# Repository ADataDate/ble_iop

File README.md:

# ble_iop
A Ryan and Mary Bluetooth Low Energy Project

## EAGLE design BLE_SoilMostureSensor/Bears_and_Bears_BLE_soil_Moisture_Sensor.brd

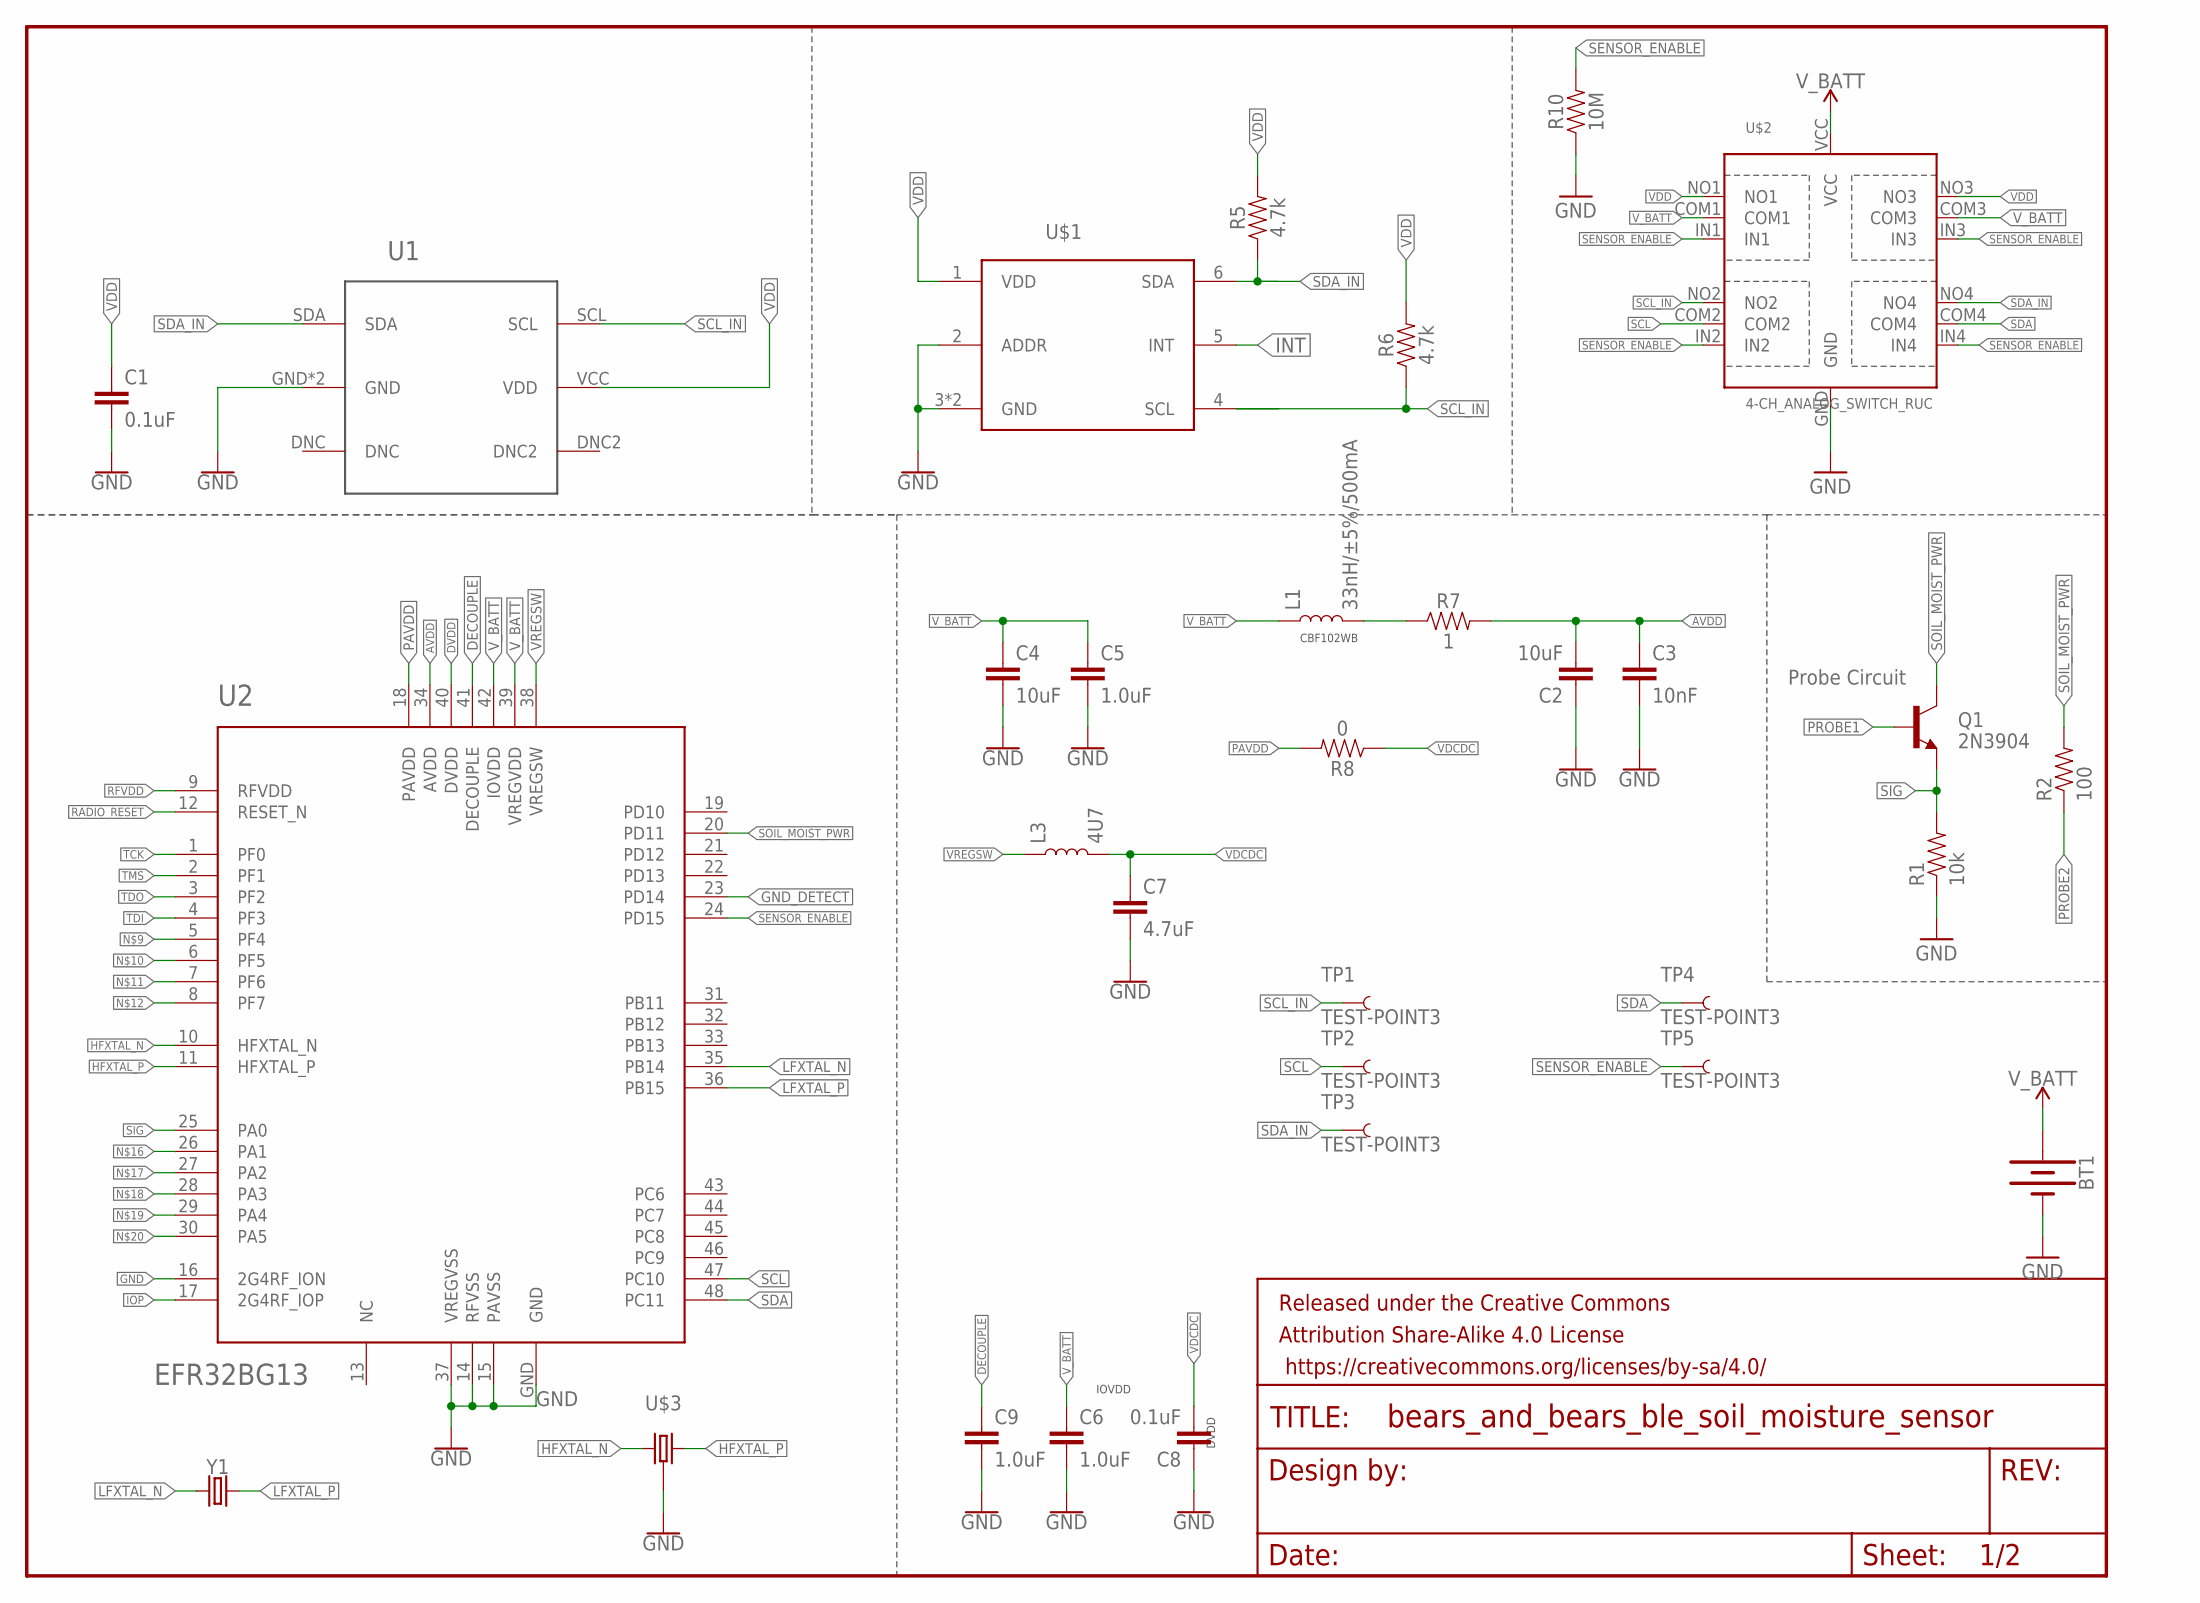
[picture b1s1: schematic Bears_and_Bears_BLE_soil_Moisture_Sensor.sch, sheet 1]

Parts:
BT1: BATTERY-20MM_SMD_4LEGS_OVERPASTE; BATTCON_20MM_4LEGS_OVERPASTE
C1, C8: 0.1uF; 0603
C2, C4: 10uF; 0603
C3: 10nF; 0603
C5, C6, C9: 1.0uF; 0603
C7: 4.7uF; 0603
FRAME1: FRAME-LETTER; CREATIVE_COMMONS
L1: 33nH/±5%/500mA; 0603
L3: 4U7; 1212(3030METRIC)
Q1: 2N3904; SOT23-3
R1: 10k; 0603-RES
R2: 100; 0603-RES
R5, R6: 4.7k; 0603
R7: 1; 0603
R8: 0; 0603
R10: 10M; 0603
TP1, TP2, TP3, TP4, TP5: TEST-POINT3; PAD.03X.03
U1: SI7021_TEMP_HUMIDTY; DFN-6
U2: EFR32BG13; QFN48
U$1: OPT3001DNPT; 6PIN_USON
U$2: 4-CH_ANALOG_SWITCH_RUC; PX2QFN14_RUC
U$3: 38.4MHZ_CRYSTAL; 2.0X1.6
Y1: 32.768KHZ_LOW_FREQ_CRYSTAL; CRYSTAL_1.2X0.6

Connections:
AVDD: C2.2, C3.1, R7.2, U2.34 (AVDD)
DECOUPLE: C9.1, U2.41 (DECOUPLE)
DVDD: U2.40 (DVDD)
GND: BT1.2 (-), C1.2, C2.1, C3.2, C4.2, C5.2, C6.2, C7.2, C8.1, C9.2, R1.1, R10.1, U1.GND, U1.GND2 (GND), U2.14 (RFVSS), U2.15 (PAVSS), U2.16 (2G4RF_ION), U2.37 (VREGVSS), U2.GND, U$1.2 (ADDR), U$1.3 (GND), U$1.GND, U$2.GND, U$3.GND, U$3.GND2 (GND); also elsewhere on the board
GND_DETECT: U2.23 (PD14); also elsewhere on the board
HFXTAL_N: U2.10 (HFXTAL_N), U$3.1
HFXTAL_P: U2.11 (HFXTAL_P), U$3.3 (2)
INT: U$1.5 (INT)
IOP: U2.17 (2G4RF_IOP); also elsewhere on the board
LFXTAL_N: U2.35 (PB14), Y1.P$1 (1)
LFXTAL_P: U2.36 (PB15), Y1.P$2 (2)
unnamed: L1.2, R7.1
PAVDD: R8.2, U2.18 (PAVDD); also elsewhere on the board
PROBE1: Q1.1 (B)
PROBE2: R2.1
RADIO_RESET: U2.12 (RESET_N); also elsewhere on the board
RFVDD: U2.9 (RFVDD); also elsewhere on the board
SCL: TP2.P$1, U2.47 (PC10), U$2.COM2
SCL_IN: R6.1, TP1.P$1, U1.SCL, U$1.4 (SCL), U$2.NO2
SDA: TP4.P$1, U2.48 (PC11), U$2.COM4
SDA_IN: R5.1, TP3.P$1, U1.SDA, U$1.6 (SDA), U$2.NO4
SENSOR_ENABLE: R10.2, TP5.P$1, U2.24 (PD15), U$2.IN1, U$2.IN2, U$2.IN3, U$2.IN4
SIG: Q1.2 (E), R1.2, U2.25 (PA0)
SOIL_MOIST_PWR: Q1.3 (C), R2.2, U2.20 (PD11)
TCK: U2.1 (PF0); also elsewhere on the board
TDI: U2.4 (PF3); also elsewhere on the board
TDO: U2.3 (PF2); also elsewhere on the board
TMS: U2.2 (PF1); also elsewhere on the board
VDCDC: C7.1, C8.2, L3.P$2 (2), R8.1; also elsewhere on the board
VDD: C1.1, R5.2, R6.2, U1.VCC (VDD), U$1.1 (VDD), U$2.NO1, U$2.NO3; also elsewhere on the board
VREGSW: L3.P$1 (1), U2.38 (VREGSW)
V_BATT: BT1.1 (+), C4.1, C5.1, C6.1, L1.1, U2.39 (VREGVDD), U2.42 (IOVDD), U$2.COM1, U$2.COM3, U$2.VCC

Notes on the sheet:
Probe Circuit
CBF102WB
IOVDD
DVDD

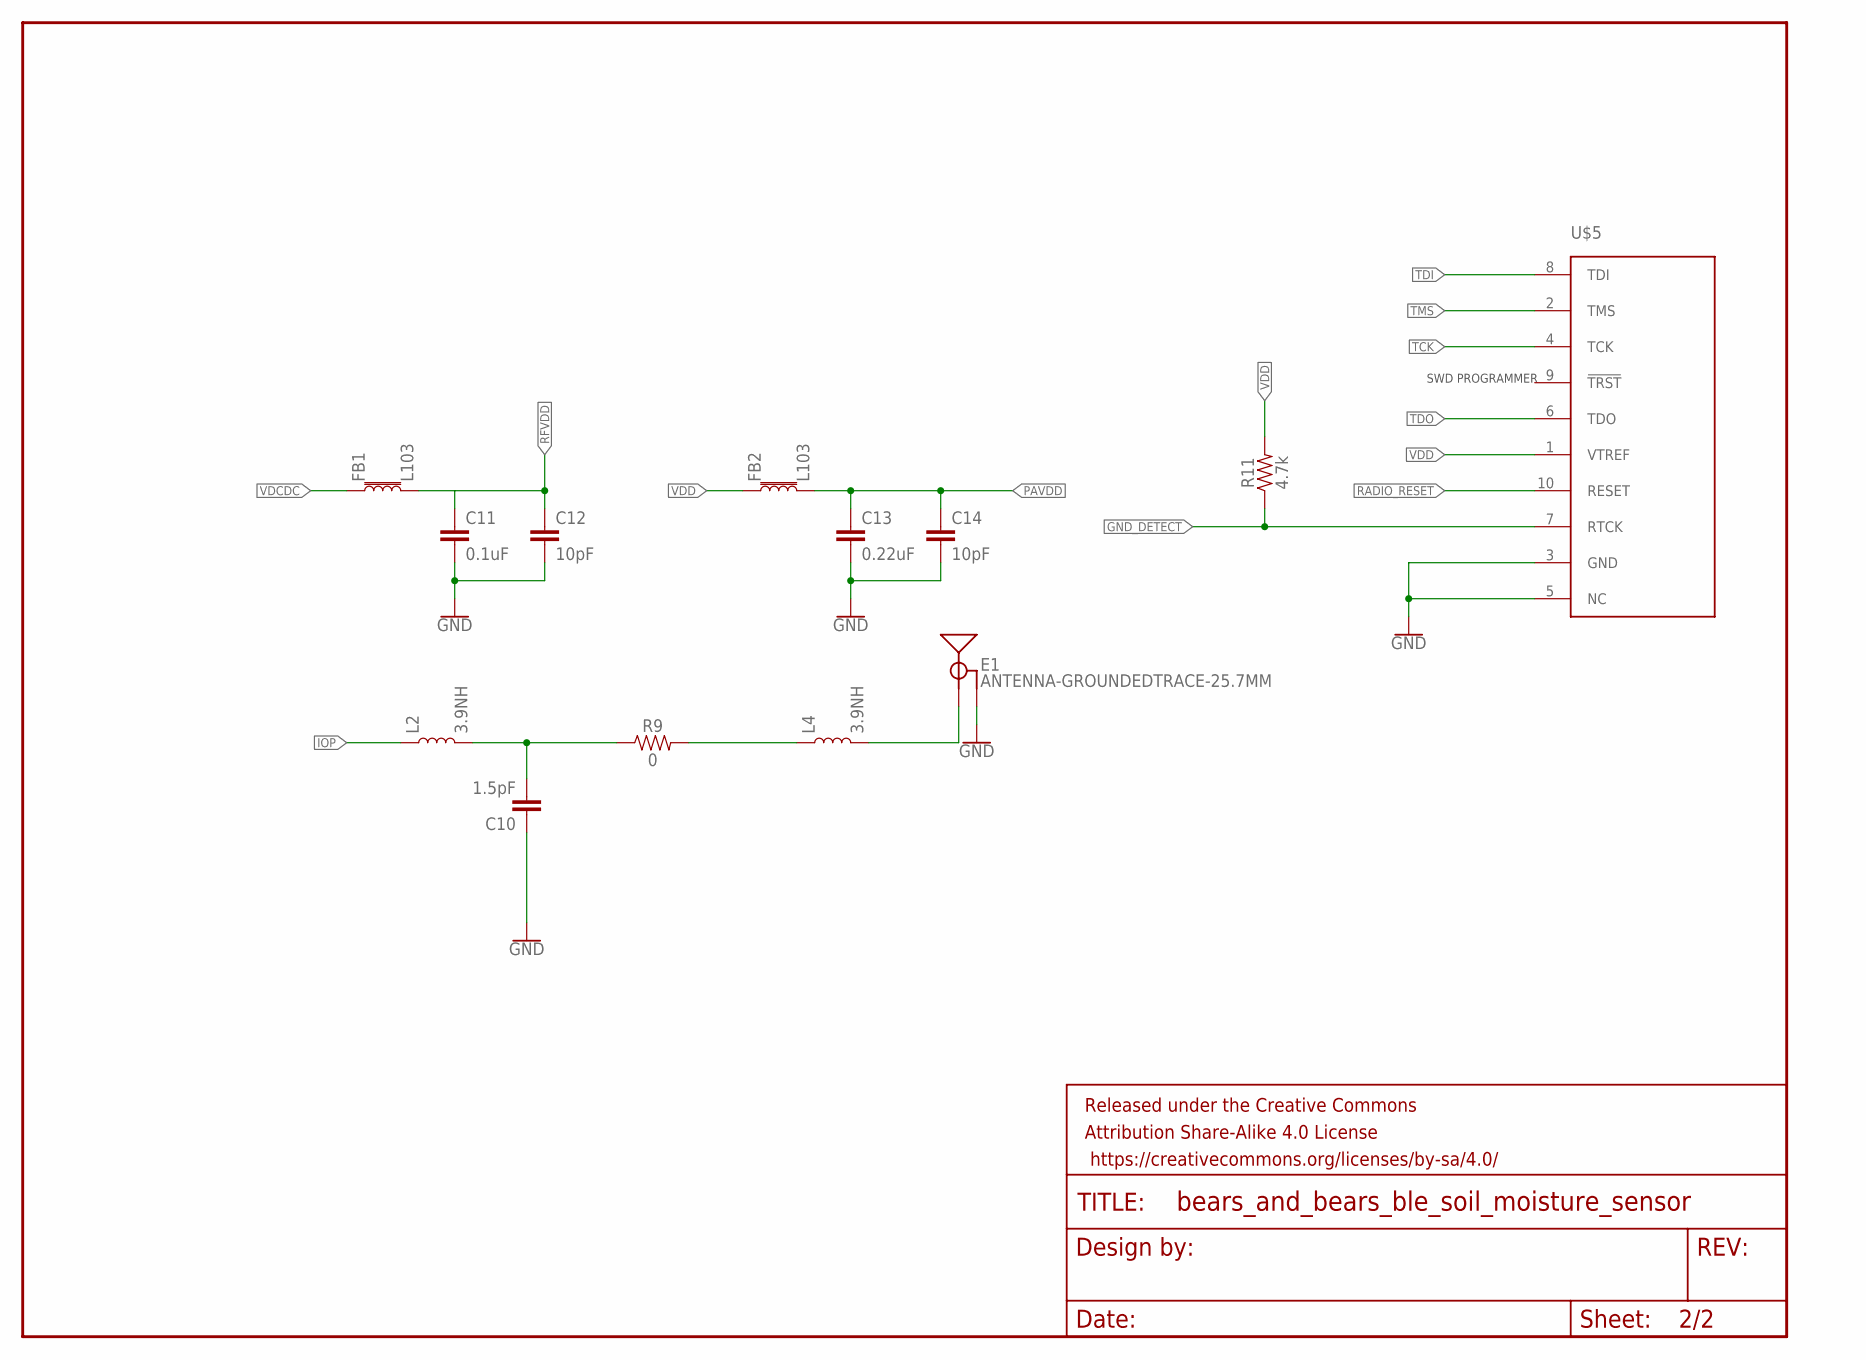
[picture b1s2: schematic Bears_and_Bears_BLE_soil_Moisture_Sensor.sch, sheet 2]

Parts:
C10: 1.5pF; 0603
C11: 0.1uF; 0603
C12, C14: 10pF; 0603
C13: 0.22uF; 0603
E1: ANTENNA-GROUNDEDTRACE-25.7MM; TRACE_ANTENNA_2.4GHZ_25.7MM
FB1, FB2: L103; 0603
FRAME2: FRAME-LETTER; CREATIVE_COMMONS
L2, L4: 3.9NH; 0402
R9: 0; 0805
R11: 4.7k; 0603
U$5: TC2050-MCP-NL; TC2030-MCP-NL

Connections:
GND: C10.1, C11.2, C12.2, C13.2, C14.2, E1.GND, E1.GND2 (GND), U$5.3 (GND), U$5.5 (NC); also elsewhere on the board
GND_DETECT: R11.1, U$5.7 (RTCK); also elsewhere on the board
IOP: L2.1; also elsewhere on the board
unnamed: C10.2, L2.2, R9.1
unnamed: L4.1, R9.2
unnamed: E1.ANT (SIGNAL), L4.2
PAVDD: C13.1, C14.1, FB2.2; also elsewhere on the board
RADIO_RESET: U$5.10 (RESET); also elsewhere on the board
RFVDD: C11.1, C12.1, FB1.2; also elsewhere on the board
TCK: U$5.4 (TCK); also elsewhere on the board
TDI: U$5.8 (TDI); also elsewhere on the board
TDO: U$5.6 (TDO); also elsewhere on the board
TMS: U$5.2 (TMS); also elsewhere on the board
VDCDC: FB1.1; also elsewhere on the board
VDD: FB2.1, R11.2, U$5.1 (VTREF); also elsewhere on the board

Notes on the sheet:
SWD PROGRAMMER

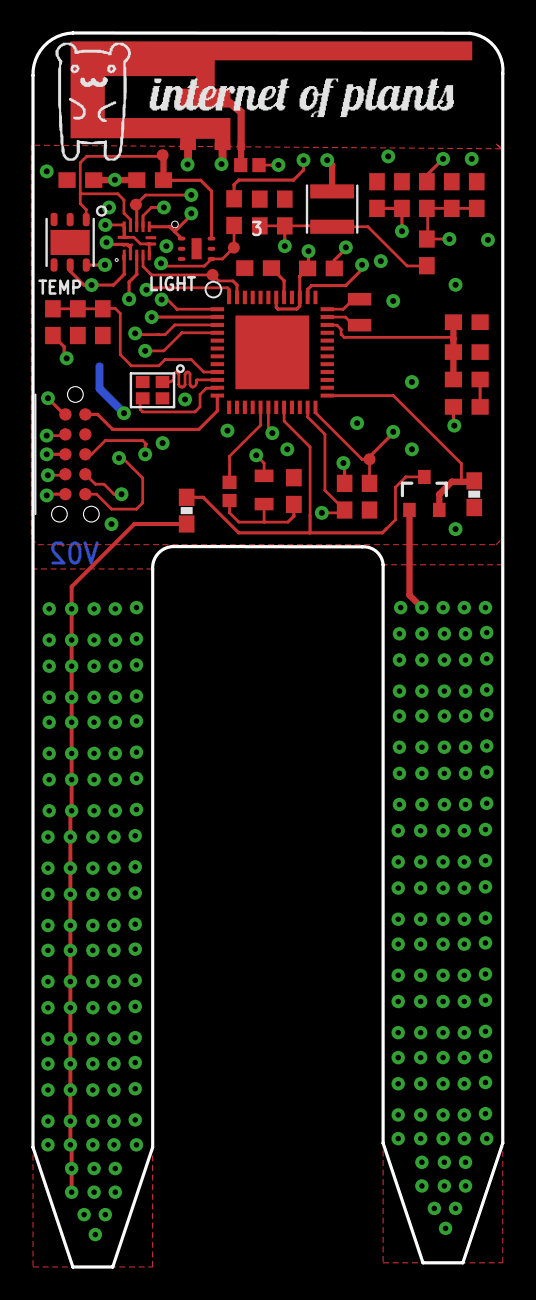
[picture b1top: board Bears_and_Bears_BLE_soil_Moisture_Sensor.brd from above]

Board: 4 copper layers, 29.9 x 78.6 mm, 48 parts (1 on the bottom side), 31 nets.

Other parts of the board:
U$4: CAPTURE#PNG
U$6: INTERNET_OF_PLANTS0

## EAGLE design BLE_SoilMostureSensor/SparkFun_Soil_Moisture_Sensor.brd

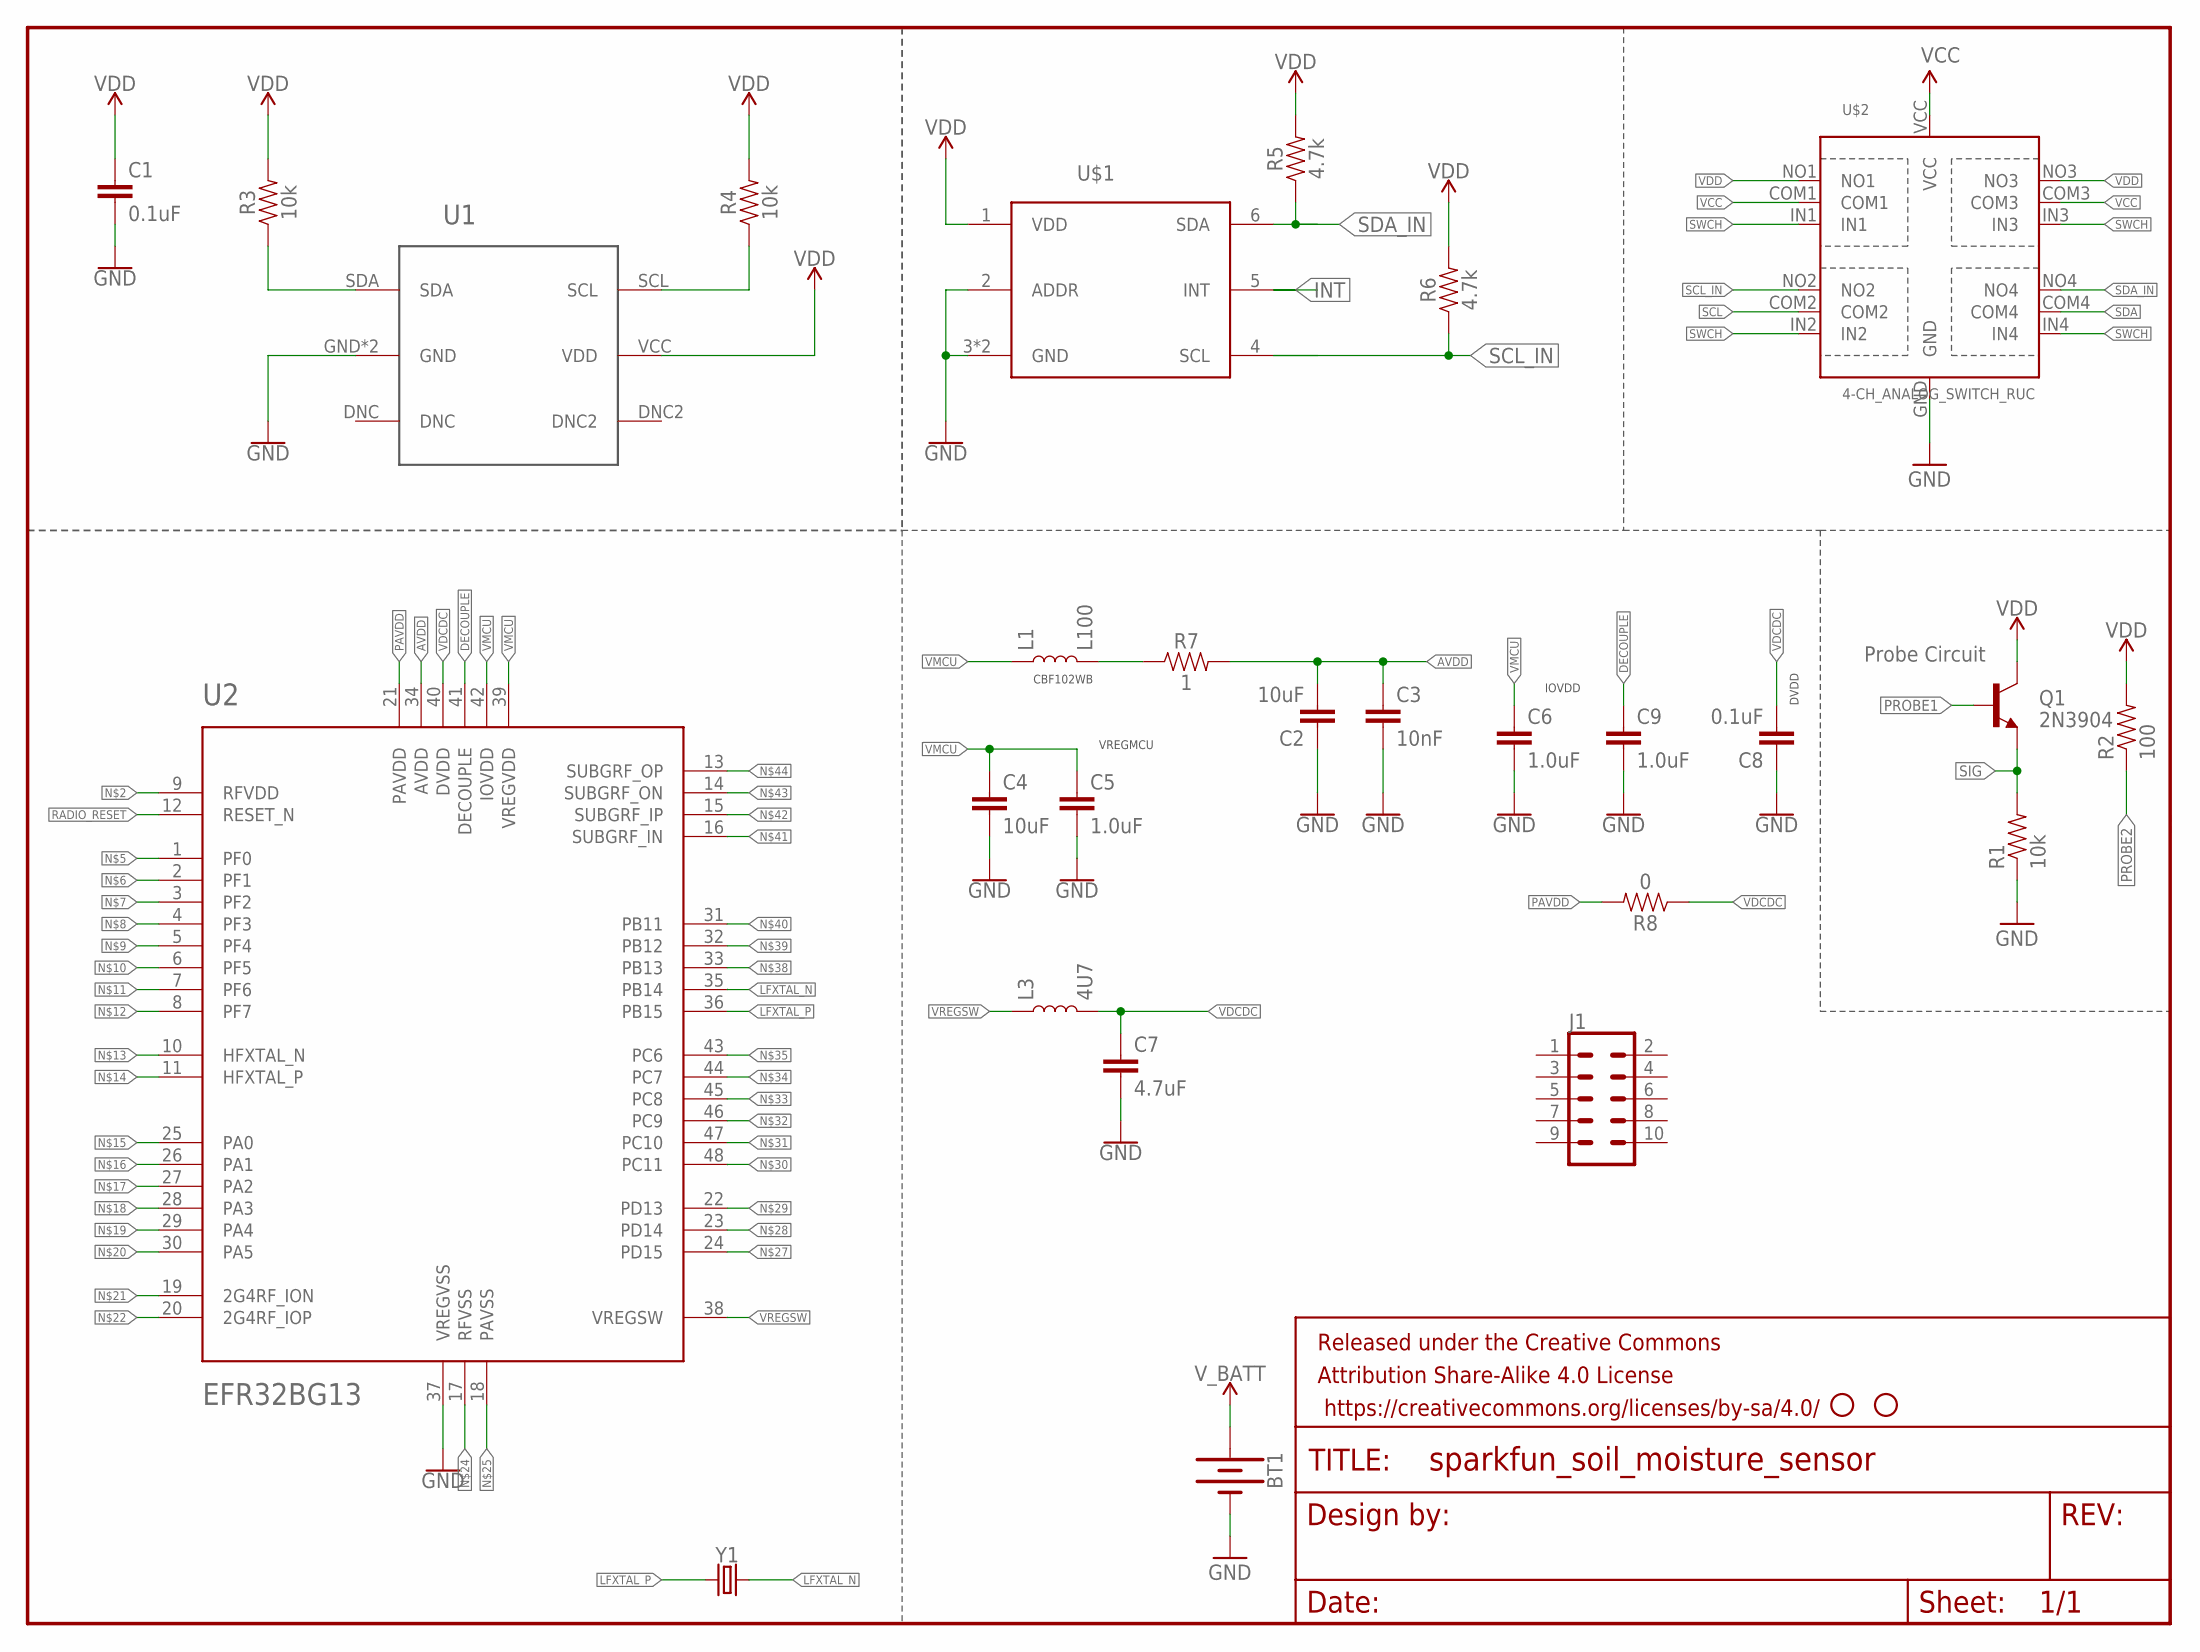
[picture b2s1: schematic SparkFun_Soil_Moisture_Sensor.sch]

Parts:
BT1: BATTERY-12MM_SMD; BATTCON_12MM
C1, C8: 0.1uF; 0603
C2, C4: 10uF; 0603
C3: 10nF; 0603
C5, C6, C9: 1.0uF; 0603
C7: 4.7uF; 0603
FRAME1: FRAME-LETTER; CREATIVE_COMMONS
J1: CONN_05X20.05_IN_PTH_SILK; 2X5_PTH_SILK_.05
L1: L100; 0603
L3: 4U7; 1212(3030METRIC)
Q1: 2N3904; SOT23-3
R1: 10k; 0603-RES
R2: 100; 0603-RES
R3, R4: 10k; 0603
R5, R6: 4.7k; 0603
R7: 1; 0603
R8: 0; 0603
STANDOFF1, STANDOFF2: STAND-OFF
U1: SI7021_TEMP_HUMIDTY; DFN-6
U2: EFR32BG13; QFN48
U$1: OPT3001DNPT; 6PIN_USON
U$2: 4-CH_ANALOG_SWITCH_RUC; PX2QFN14_RUC
Y1: 32.768KHZ_LOW_FREQ_CRYSTAL; CRYSTAL_1.2X0.6

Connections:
AVDD: C2.2, C3.1, R7.2, U2.34 (AVDD)
DECOUPLE: C9.1, U2.41 (DECOUPLE)
GND: BT1.GND (-), C1.2, C2.1, C3.2, C4.2, C5.2, C6.2, C7.2, C8.1, C9.2, R1.1, U1.GND, U1.GND2 (GND), U2.37 (VREGVSS), U$1.2 (ADDR), U$1.3 (GND), U$1.GND, U$2.GND
INT: U$1.5 (INT)
LFXTAL_N: U2.35 (PB14), Y1.P$2 (2)
LFXTAL_P: U2.36 (PB15), Y1.P$1 (1)
unnamed: R4.1, U1.SCL
unnamed: R3.1, U1.SDA
unnamed: L1.2, R7.1
PAVDD: R8.2, U2.21 (PAVDD)
PROBE1: Q1.1 (B)
PROBE2: R2.1
RADIO_RESET: U2.12 (RESET_N)
SCL: U$2.COM2
SCL_IN: R6.1, U$1.4 (SCL), U$2.NO2
SDA: U$2.COM4
SDA_IN: R5.1, U$1.6 (SDA), U$2.NO4
SIG: Q1.2 (E), R1.2
SWCH: U$2.IN1, U$2.IN2, U$2.IN3, U$2.IN4
VCC: U$2.COM1, U$2.COM3, U$2.VCC
VDCDC: C7.1, C8.2, L3.P$2 (2), R8.1, U2.40 (DVDD)
VDD: C1.1, Q1.3 (C), R2.2, R3.2, R4.2, R5.2, R6.2, U1.VCC (VDD), U$1.1 (VDD), U$2.NO1, U$2.NO3
VMCU: C4.1, C5.1, C6.1, L1.1, U2.39 (VREGVDD), U2.42 (IOVDD)
VREGSW: L3.P$1 (1), U2.38 (VREGSW)
V_BATT: BT1.PWR@1 (+)

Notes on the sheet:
Probe Circuit
CBF102WB
VREGMCU
IOVDD
DVDD

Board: 2 copper layers, 30 parts (1 on the bottom side), 18 nets, no tracks yet.

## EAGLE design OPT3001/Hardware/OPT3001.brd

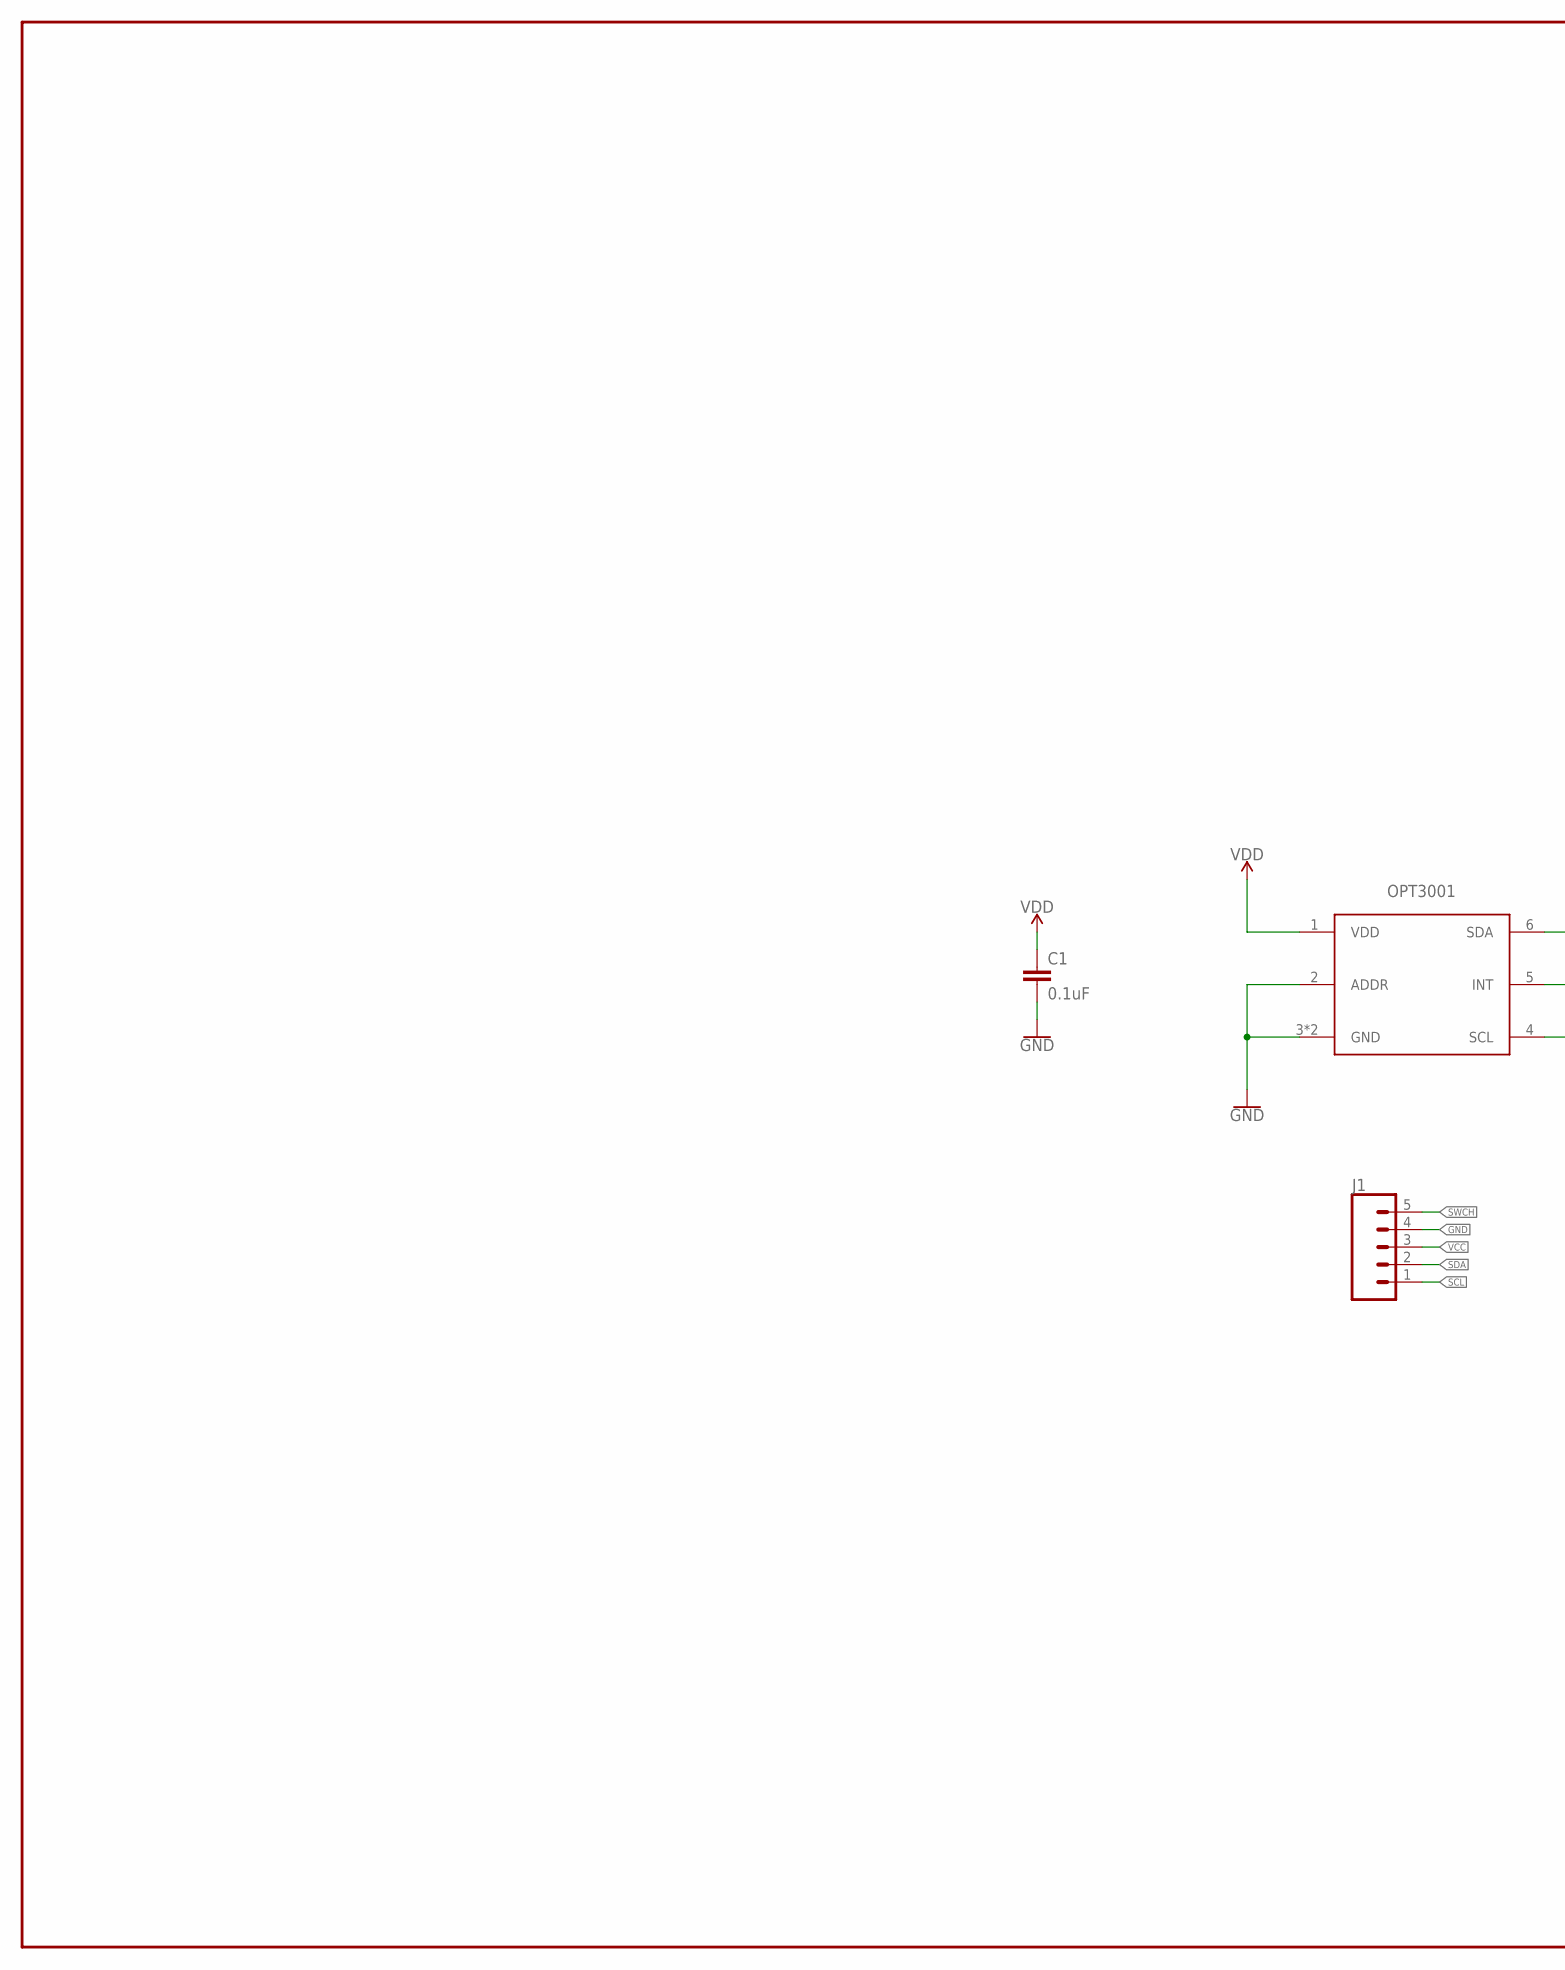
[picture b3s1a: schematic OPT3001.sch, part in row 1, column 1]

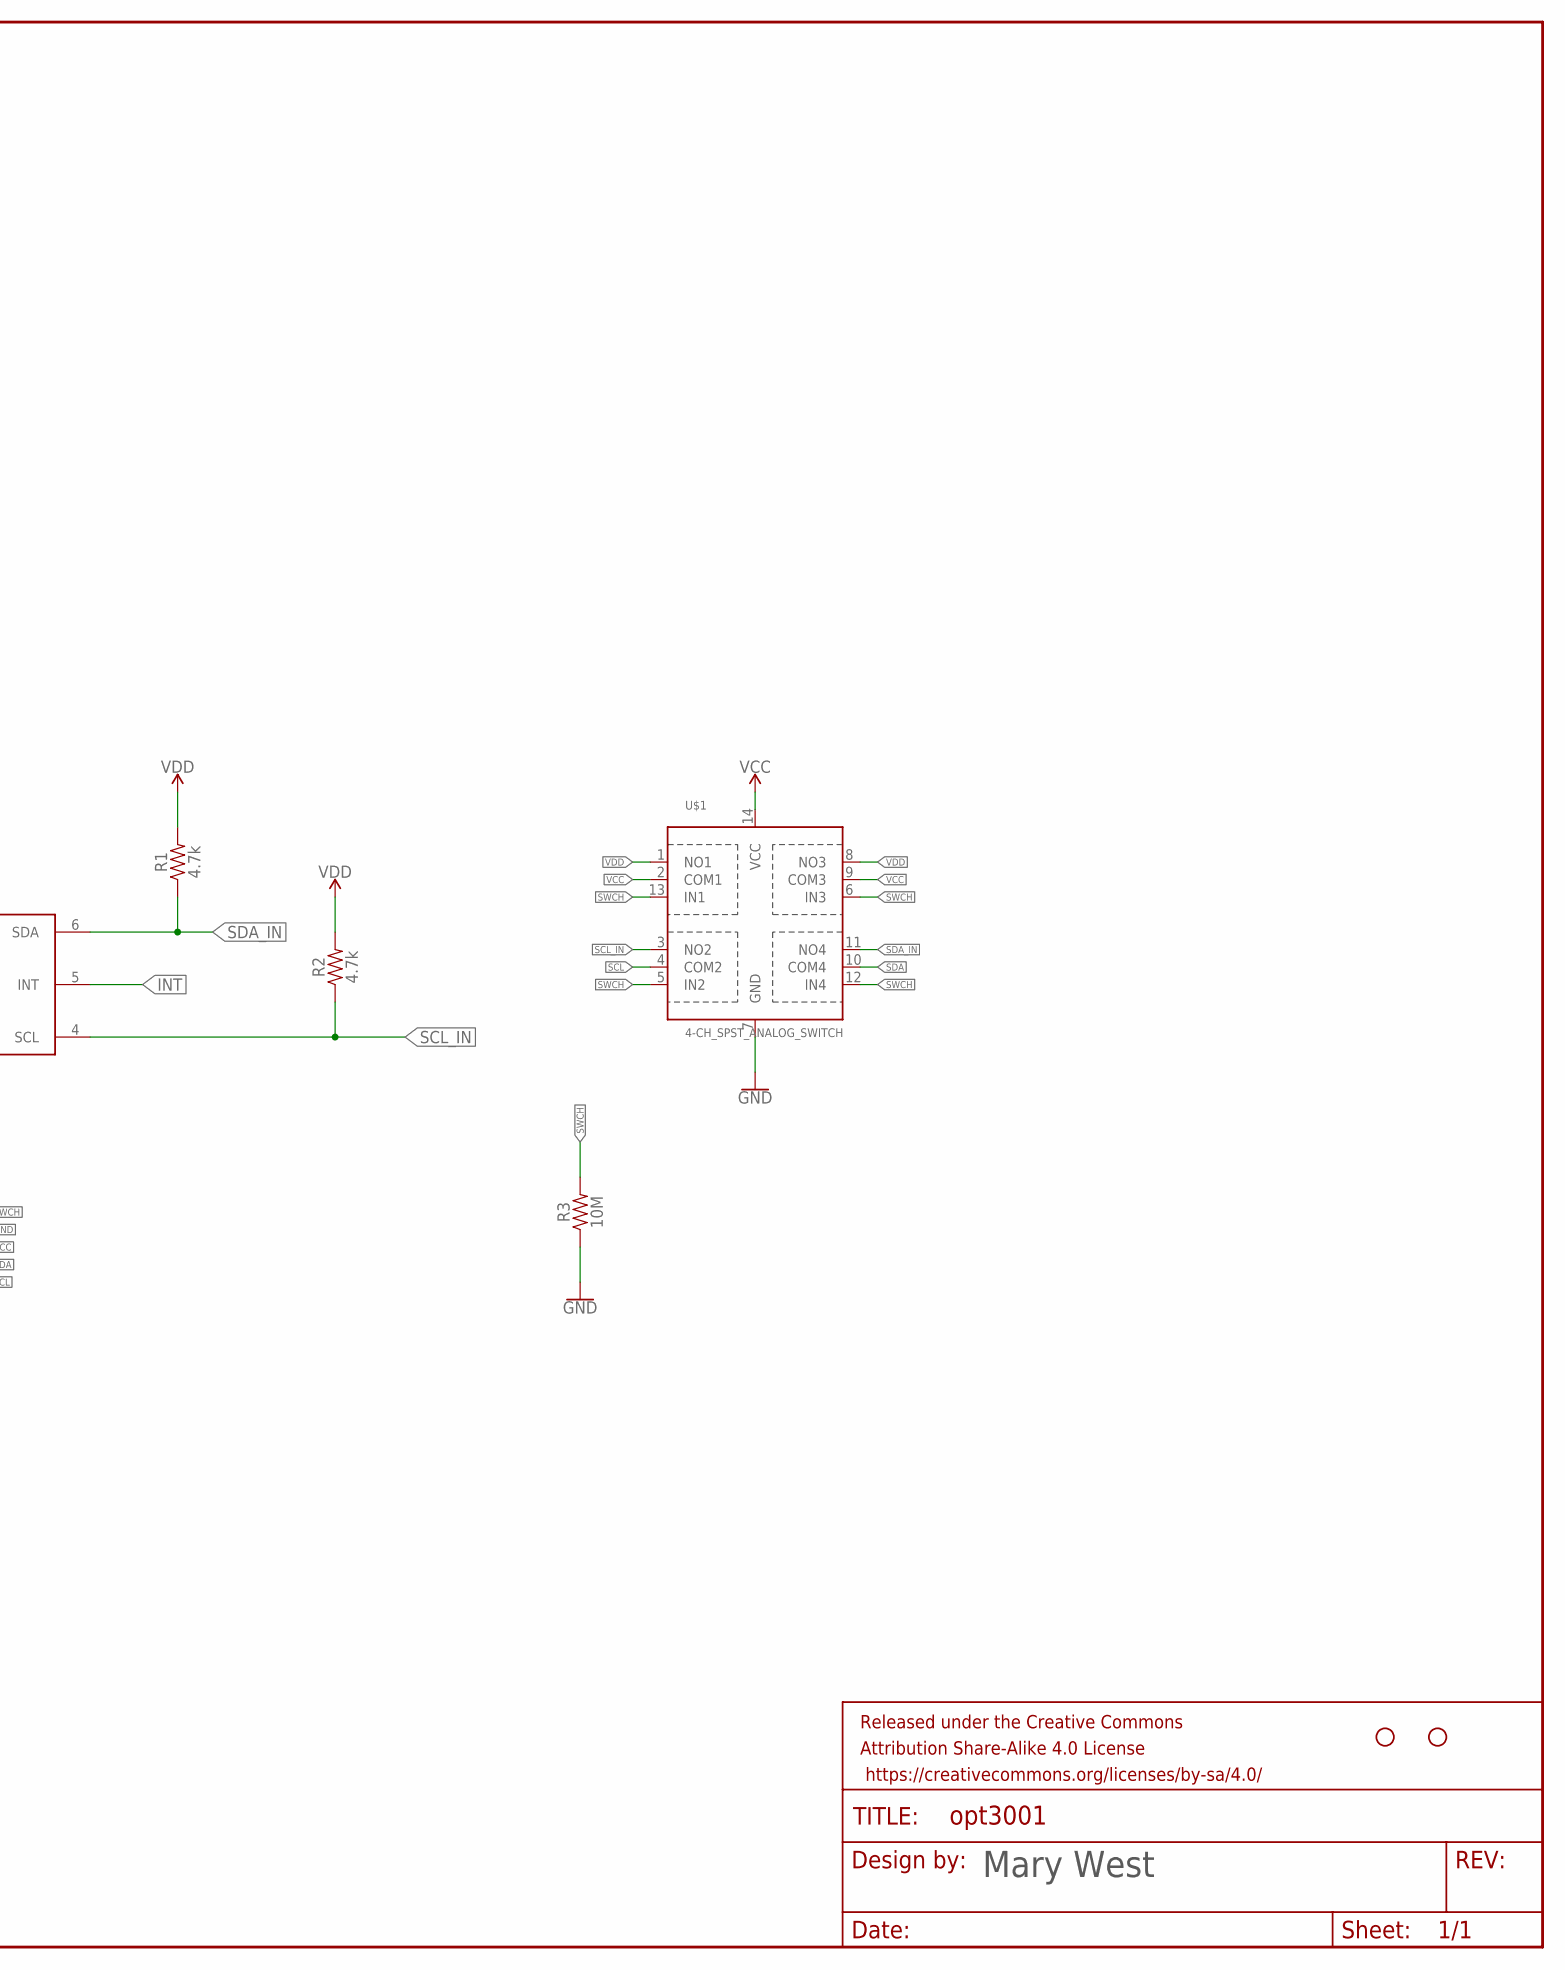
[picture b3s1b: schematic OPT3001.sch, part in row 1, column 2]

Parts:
C1: 0.1uF; 0603
FRAME1: FRAME-LEDGER; CREATIVE_COMMONS
H1, H2: STAND-OFF
J1: CONN_05; 1X05
OPT3001: OPT3001DNPT; 6PIN_USON
R1, R2: 4.7k; 0603
R3: 10M; 0603
U$1: 4-CH_SPST_ANALOG_SWITCH; TSSOP14

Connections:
GND: C1.2, J1.4, OPT3001.2 (ADDR), OPT3001.3 (GND), OPT3001.GND, R3.1, U$1.7 (GND)
INT: OPT3001.5 (INT)
SCL: J1.1, U$1.4 (COM2)
SCL_IN: OPT3001.4 (SCL), R2.1, U$1.3 (NO2)
SDA: J1.2, U$1.10 (COM4)
SDA_IN: OPT3001.6 (SDA), R1.1, U$1.11 (NO4)
SWCH: J1.5, R3.2, U$1.5 (IN2), U$1.6 (IN3), U$1.12 (IN4), U$1.13 (IN1)
VCC: J1.3, U$1.2 (COM1), U$1.9 (COM3), U$1.14 (VCC)
VDD: C1.1, OPT3001.1 (VDD), R1.2, R2.2, U$1.1 (NO1), U$1.8 (NO3)

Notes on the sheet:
Mary West

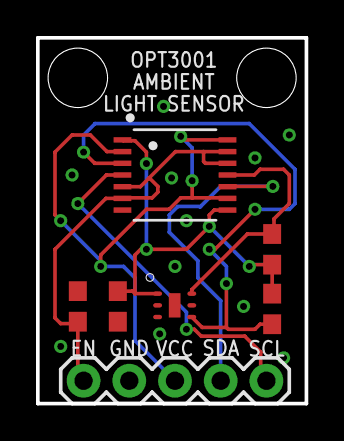
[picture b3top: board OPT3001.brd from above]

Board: 2 copper layers, 14.9 x 20.3 mm, 10 parts (0 on the bottom side), 8 nets.

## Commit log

2018-02-24 Add BootLoader
2018-03-20 Adding hardware Files
2018-04-09 Adding supporting hardware for BLE module
2018-04-23 updating Soil Moisture Design
2018-04-27 fixing antenna
2018-04-29 Remove unused backup files
2018-04-30 first prototype
2018-06-04 updating sch - 12c, power
2019-01-05 Make required changes:
    - Rotate temp sensor and reroute
    - Route AVDD to MCU
    - Route PAVDD to MCU
    - Change SWD jack to POGO type
2019-01-06 1. MDE BOARD SMALLER, RE DID LAYOUT, DELETED SILK. TO DO: REPLACE SILK, FINISH ROUTING, POLYGON PROCESSING, IN DEPTH DESIGN REVIEW, REVIEW nrf ANTENNA REQUIREMENT AND LAYOUT SUGGESTIONS
2019-01-06 routing completed and ready for review

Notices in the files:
parts and their libraries:
SparkFun-DiscreteSemi: Licensing: Creative Commons ShareAlike 4.0 International - https://creativecommons.org/licenses/by-sa/4.0
SparkFun-Aesthetics: Released under the Creative Commons Attribution Share-Alike 4.0 License
SparkFun-Aesthetics: https://creativecommons.org/licenses/by-sa/4.0
